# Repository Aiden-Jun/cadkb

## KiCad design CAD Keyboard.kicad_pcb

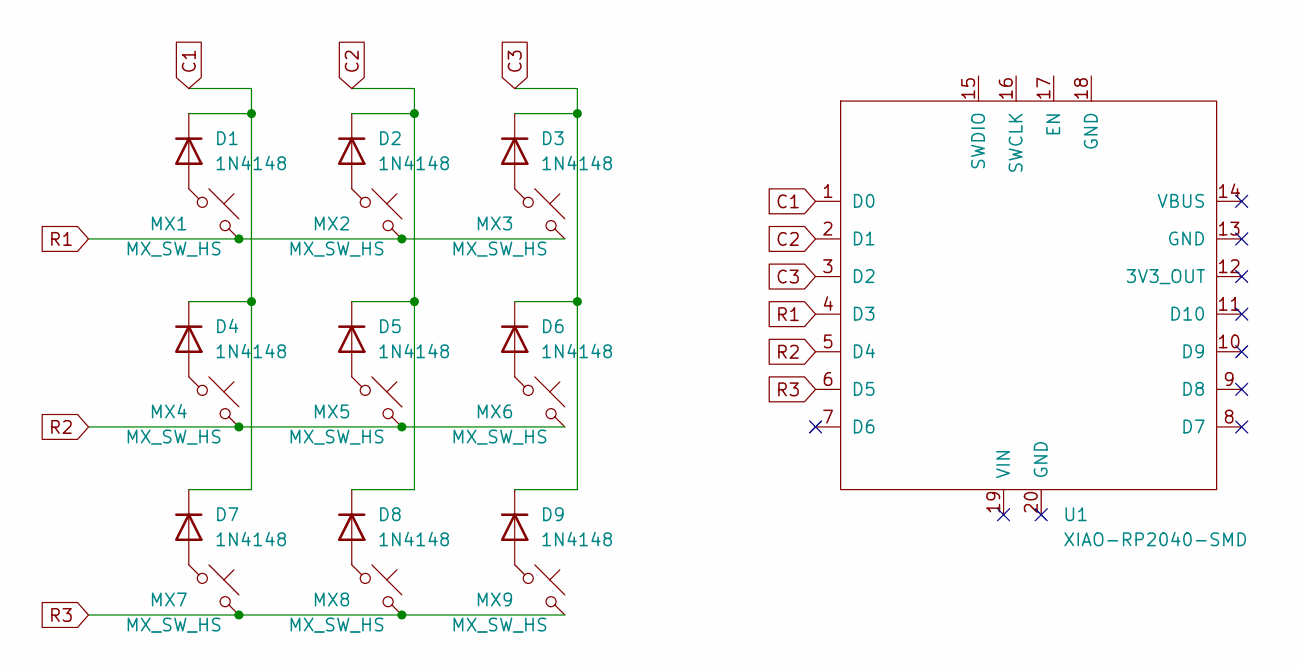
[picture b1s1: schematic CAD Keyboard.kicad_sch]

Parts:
D1, D2, D3, D4, D5, D6, D7, D8, D9: 1N4148; D_DO-35_SOD27_P7.62mm_Horizontal
MX1, MX2, MX3, MX4, MX5, MX6, MX7, MX8, MX9: MX_SW_HS; SW_MX_HS_CPG151101S11_1u
U1: XIAO-RP2040-SMD

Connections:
C1: D1.1 (K), D4.1 (K), D7.1 (K), U1.1 (D0)
C2: D2.1 (K), D5.1 (K), D8.1 (K), U1.2 (D1)
C3: D3.1 (K), D6.1 (K), D9.1 (K), U1.3 (D2)
unnamed: D1.2 (A), MX1.1
unnamed: D2.2 (A), MX2.1
unnamed: D3.2 (A), MX3.1
unnamed: D4.2 (A), MX4.1
unnamed: D5.2 (A), MX5.1
unnamed: D6.2 (A), MX6.1
unnamed: D7.2 (A), MX7.1
unnamed: D8.2 (A), MX8.1
unnamed: D9.2 (A), MX9.1
R1: MX1.2, MX2.2, MX3.2, U1.4 (D3)
R2: MX4.2, MX5.2, MX6.2, U1.5 (D4)
R3: MX7.2, MX8.2, MX9.2, U1.6 (D5)

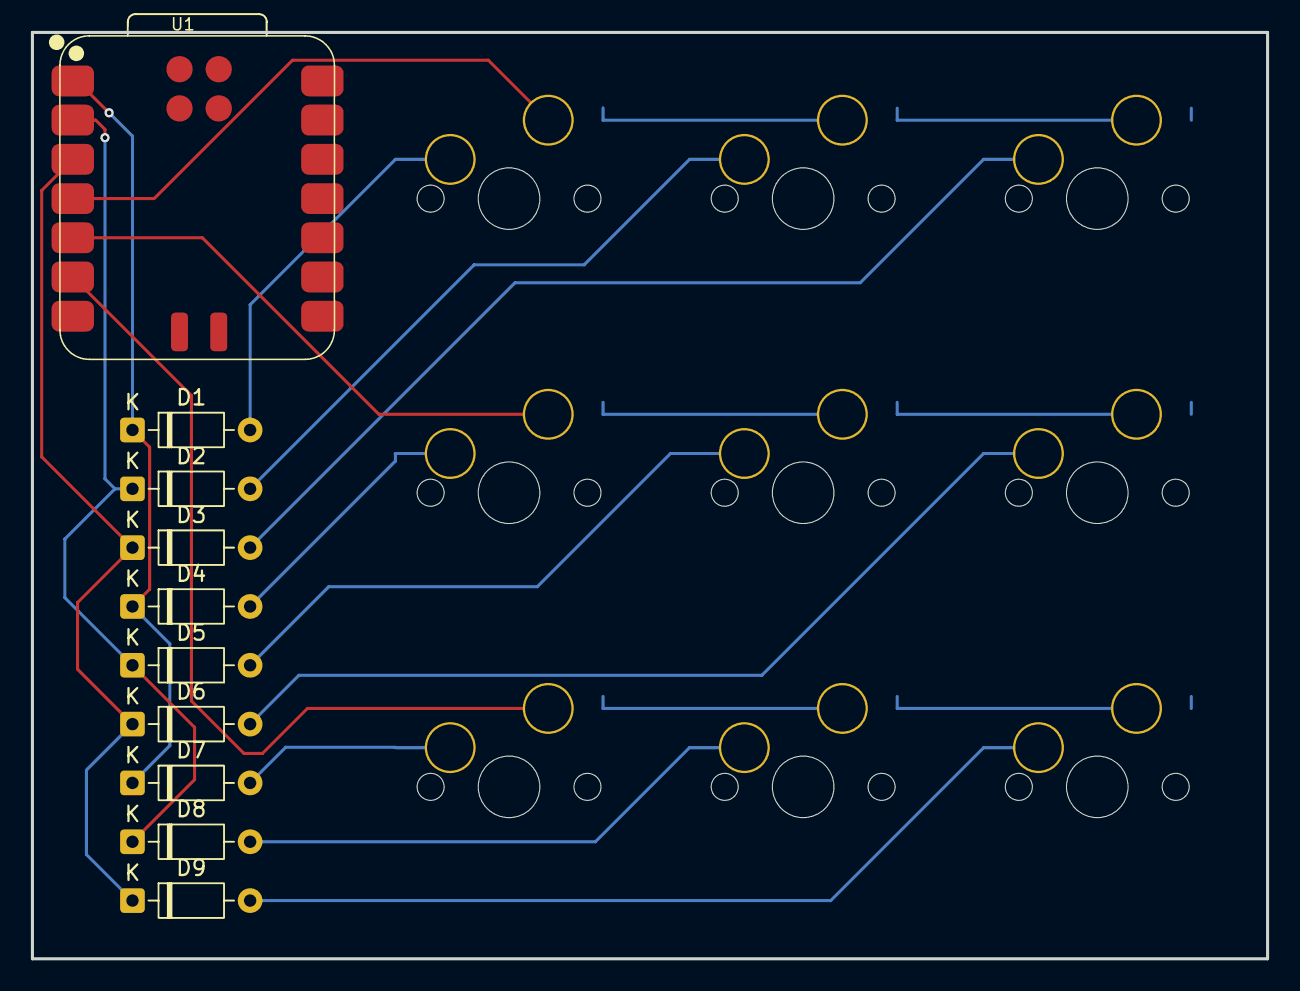
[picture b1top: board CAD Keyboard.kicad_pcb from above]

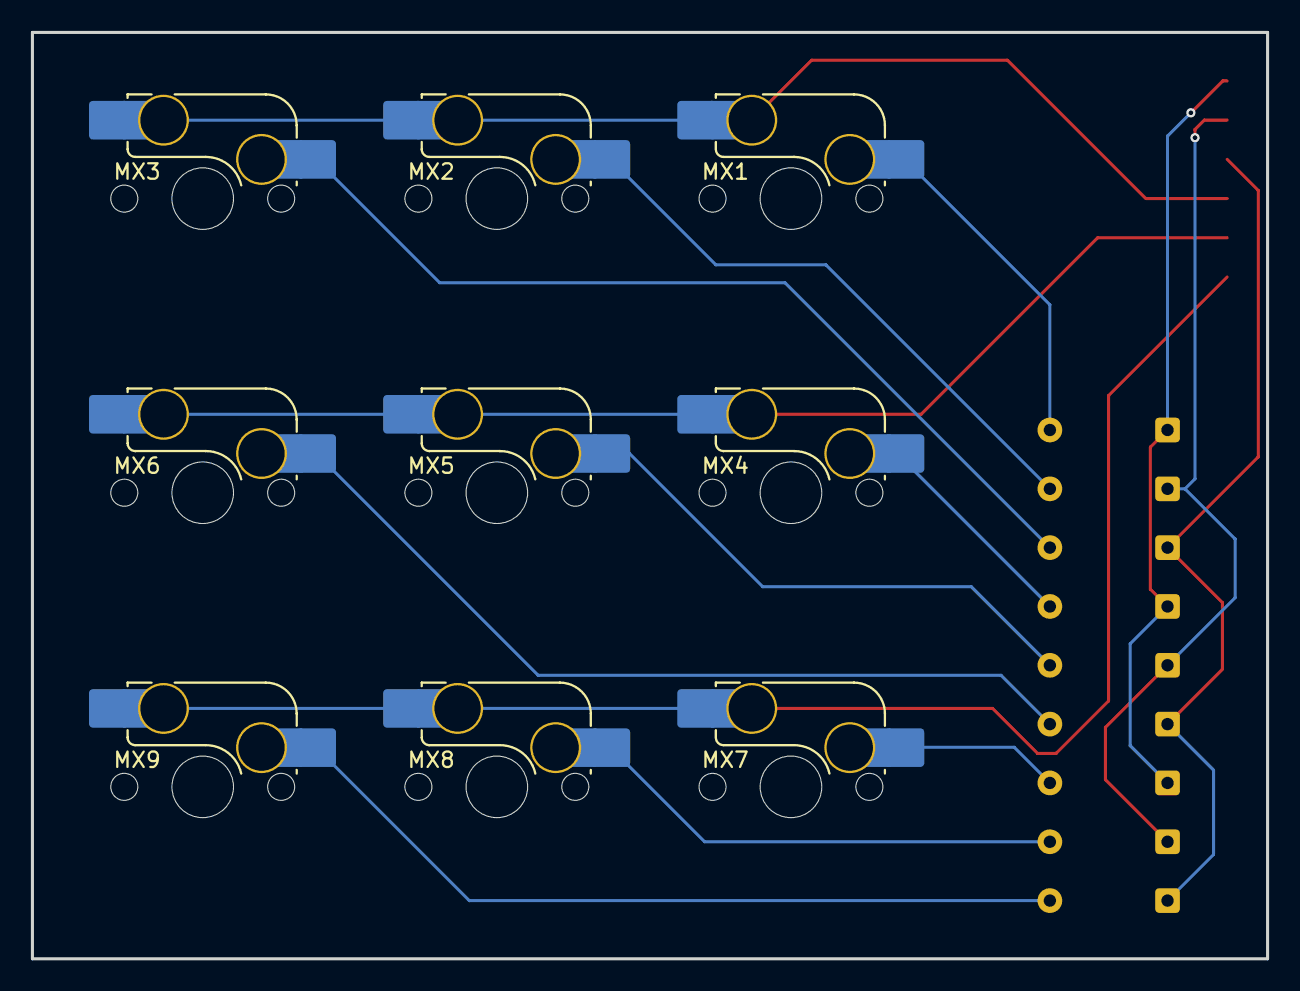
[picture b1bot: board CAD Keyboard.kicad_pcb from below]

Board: 2 copper layers, 80.0 x 60.0 mm, 19 parts (9 on the bottom side), 15 nets.
